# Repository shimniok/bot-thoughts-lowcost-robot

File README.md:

# bot-thoughts-lowcost-robot

Entry for 2012 African Robotics Network Challenge to build a $10, educational robot.

[Bot Thoughts Blog article](https://www.bot-thoughts.com/2012/09/entry-for-afron-10-dollar-robot-design.html)

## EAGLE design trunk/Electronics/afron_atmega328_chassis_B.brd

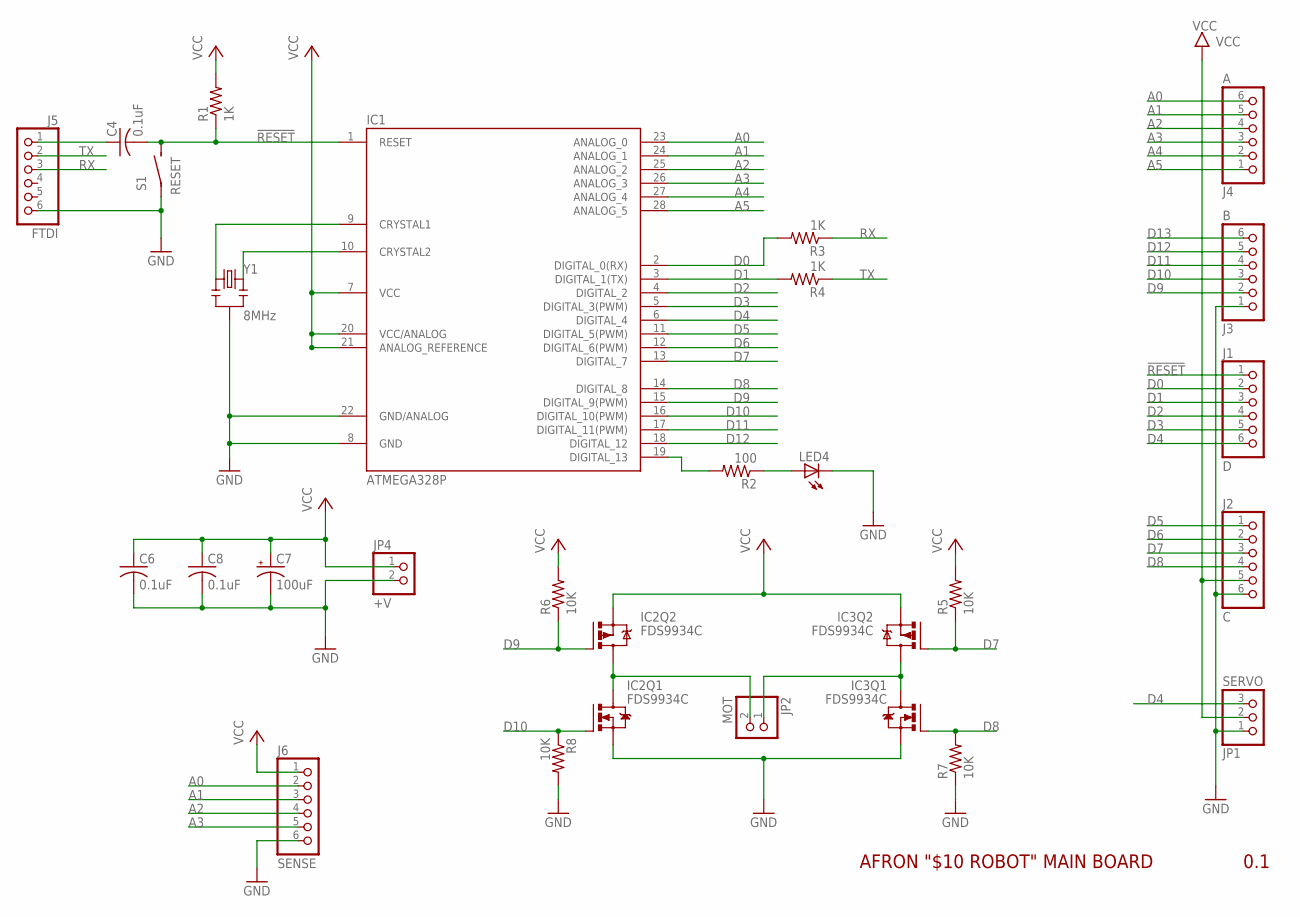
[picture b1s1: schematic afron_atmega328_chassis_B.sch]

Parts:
C4, C6, C8: 0.1uF; C050-024X044
C7: 100uF; E2,5-6
IC1: ATMEGA328P; DIL28-3
IC2, IC3: FDS9934C; SOIC8
J1: D; 1X06
J2: C; 1X06
J3: B; 1X06
J4: A; 1X06
J5: FTDI; 1X06
J6: SENSE; 1X06
JP1: SERVO; 1X03
JP2: MOT; 1X02-S
JP4: +V; 1X02-S
LED4: LED3MM
R1, R3, R4: 1K; 0204/5
R2: 100; 0204/5
R5, R6, R7, R8: 10K; 0204/5
S1: RESET; 6MMTACTILE
Y1: 8MHz; RESONATOR-PTH

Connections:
!RESET: C4.2, IC1.1 (RESET), J1.1, R1.1, S1.P$2 (S)
A0: IC1.23 (ANALOG_0), J4.6, J6.2
A1: IC1.24 (ANALOG_1), J4.5, J6.3
A2: IC1.25 (ANALOG_2), J4.4, J6.4
A3: IC1.26 (ANALOG_3), J4.3, J6.5
A4: IC1.27 (ANALOG_4), J4.2
A5: IC1.28 (ANALOG_5), J4.1
D0: IC1.2 (DIGITAL_0(RX)), J1.2, R3.2
D1: IC1.3 (DIGITAL_1(TX)), J1.3, R4.2
D2: IC1.4 (DIGITAL_2), J1.4
D3: IC1.5 (DIGITAL_3(PWM)), J1.5
D4: IC1.6 (DIGITAL_4), J1.6, JP1.3
D5: IC1.11 (DIGITAL_5(PWM)), J2.1
D6: IC1.12 (DIGITAL_6(PWM)), J2.2
D7: IC1.13 (DIGITAL_7), IC3.4 (G), J2.3, R5.1
D8: IC1.14 (DIGITAL_8), IC3.2 (G), J2.4, R7.2
D9: IC1.15 (DIGITAL_9(PWM)), IC2.4 (G), J3.2, R6.1
D10: IC1.16 (DIGITAL_10(PWM)), IC2.2 (G), J3.3, R8.1
D11: IC1.17 (DIGITAL_11(PWM)), J3.4
D12: IC1.18 (DIGITAL_12), J3.5
D13: IC1.19 (DIGITAL_13), J3.6, R2.2
GND: C6.2, C7.-, C8.2, IC1.8 (GND), IC1.22 (GND/ANALOG), IC2.1 (S), IC3.1 (S), J2.6, J3.1, J5.6, J6.6, JP1.1, JP4.2, LED4.K (C), R7.1, R8.2, S1.P$1, Y1.2
MA: IC2.5 (D), IC2.6 (D), IC2.7 (D), IC2.8 (D), JP2.2
MB: IC3.5 (D), IC3.6 (D), IC3.7 (D), IC3.8 (D), JP2.1
unnamed: IC1.9 (CRYSTAL1), Y1.1
unnamed: IC1.10 (CRYSTAL2), Y1.3
unnamed: C4.1, J5.1
unnamed: LED4.A, R2.1
RX: J5.3, R3.1
TX: J5.2, R4.1
VCC: C6.1, C7.+, C8.1, IC1.7 (VCC), IC1.20 (VCC/ANALOG), IC1.21 (ANALOG_REFERENCE), IC2.3 (S), IC3.3 (S), J2.5, J6.1, JP1.2, JP4.1, R1.2, R5.2, R6.2

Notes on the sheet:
AFRON "$10 ROBOT" MAIN BOARD
0.1

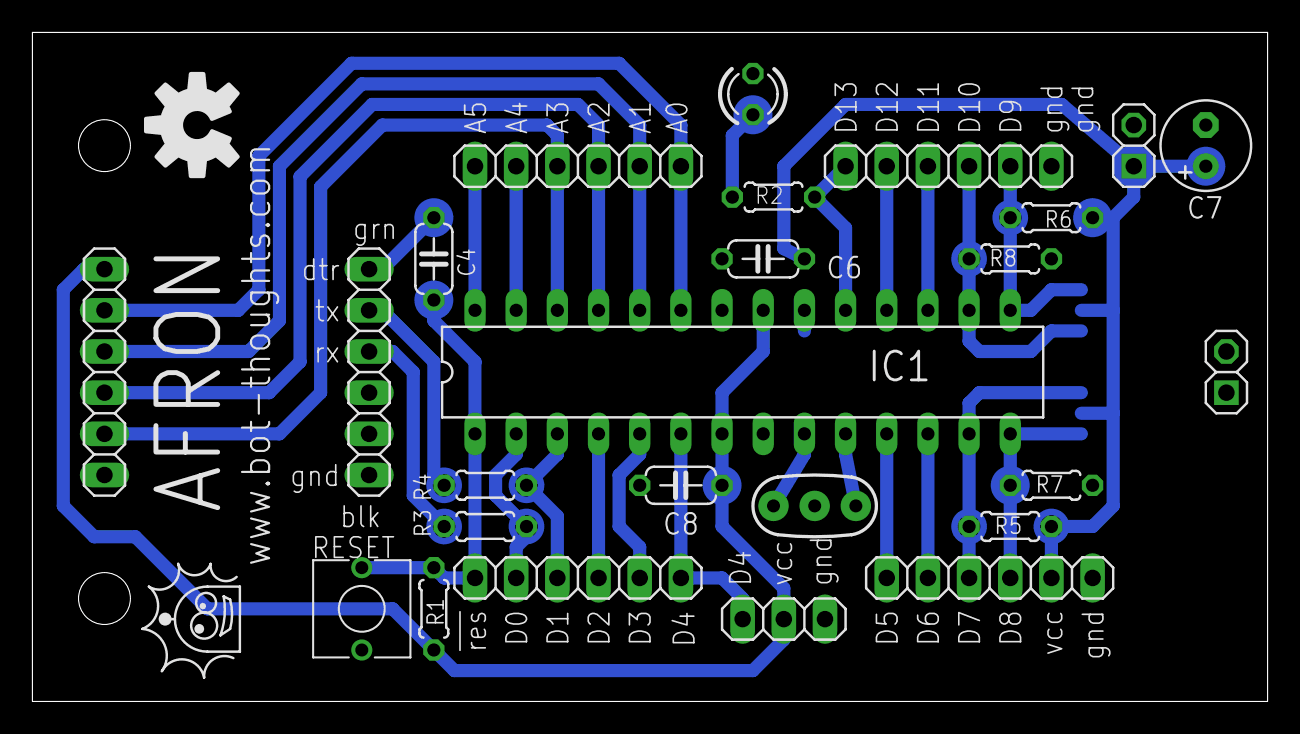
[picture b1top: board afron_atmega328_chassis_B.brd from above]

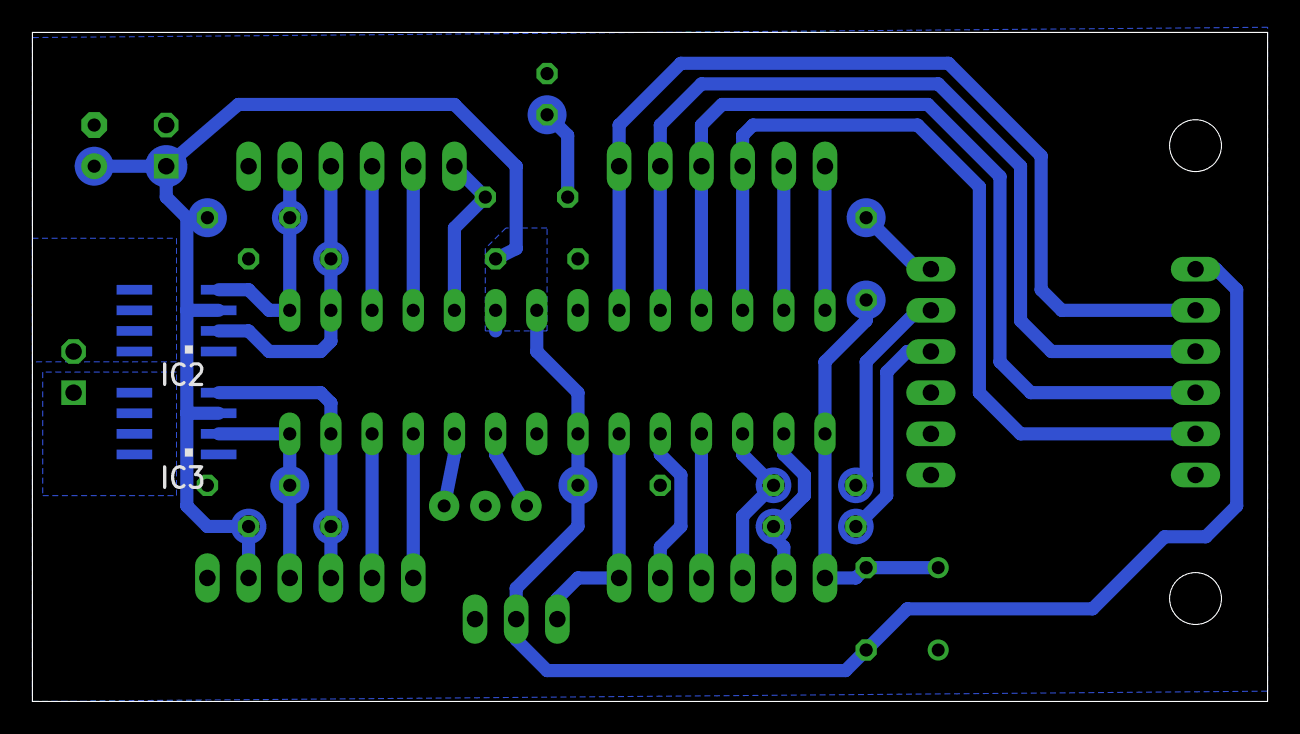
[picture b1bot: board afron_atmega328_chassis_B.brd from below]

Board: 2 copper layers, 76.2 x 41.3 mm, 27 parts (2 on the bottom side), 31 nets.

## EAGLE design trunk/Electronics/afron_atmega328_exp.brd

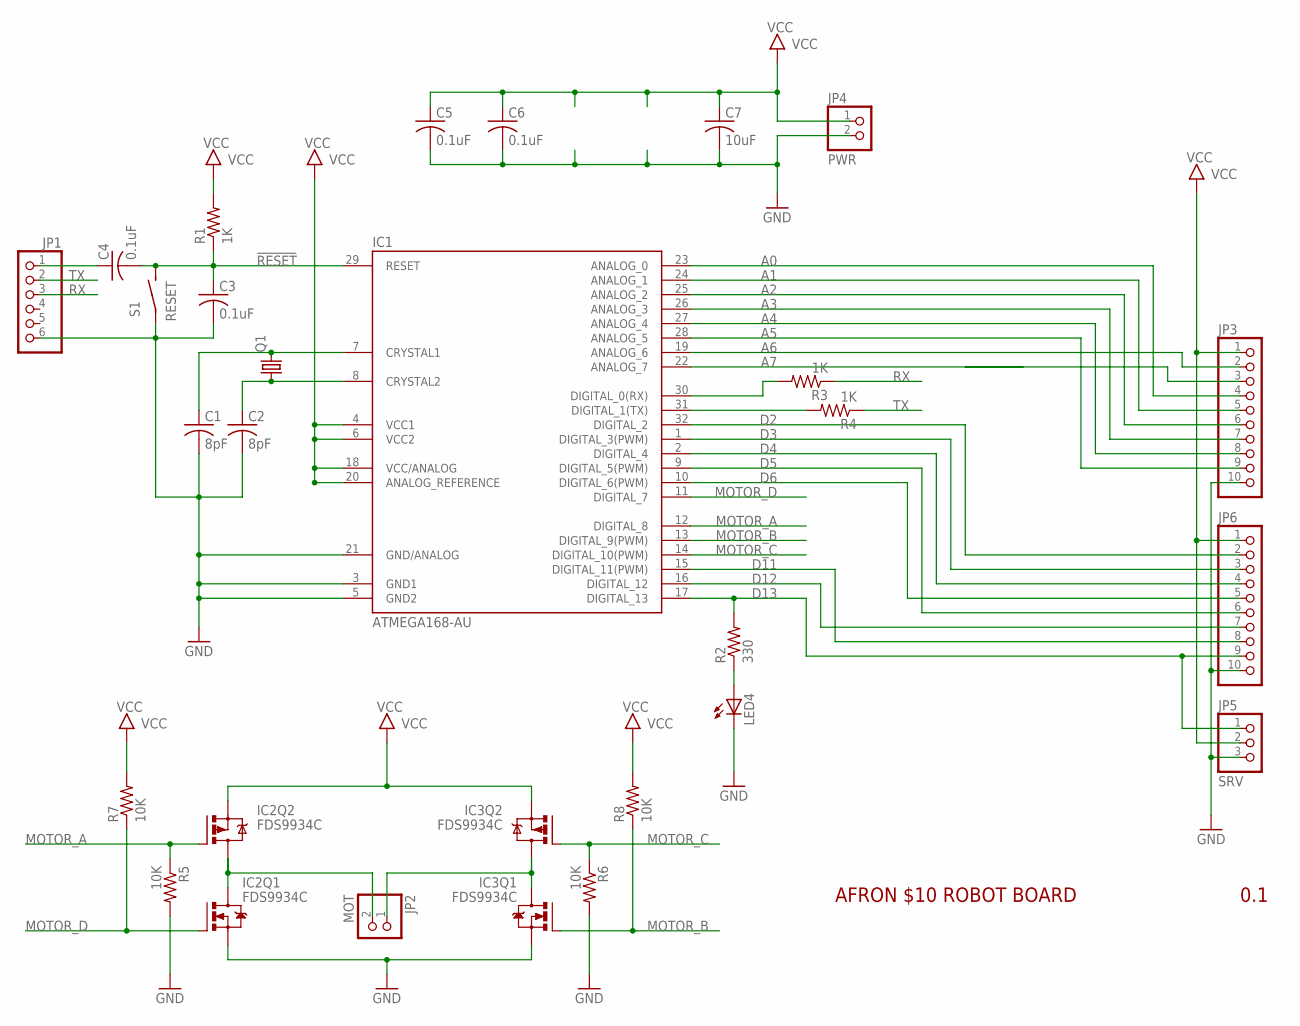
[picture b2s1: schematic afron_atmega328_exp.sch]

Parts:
C1, C2: 8pF; C0603
C3, C4, C5, C6: 0.1uF; C0603
C7: 10uF; C0805
IC1: ATMEGA168-AU; TQFP32-08
IC2, IC3: FDS9934C; SOIC8
JP1: PINHD-1X06_2.54-S; 1X06-S
JP2: MOT; 1X02-S
JP3, JP6: PINHD-1X10_2.54-S; 1X10-S
JP4: PWR; 1X02-S
JP5: SRV; 1X03-S
LED4: LEDSML0805; SML0805
Q1: CRYSTALNDK5X3; NDK_2PAD_5X3
R1, R3, R4: 1K; R0603
R2: 330; R0603
R5, R6, R7, R8: 10K; R0603
S1: RESET; 6MMTACTILE_RECT

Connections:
!RESET: C3.1, C4.2, IC1.29 (RESET), R1.1, S1.P$2 (S)
A0: IC1.23 (ANALOG_0), JP3.4
A1: IC1.24 (ANALOG_1), JP3.5
A2: IC1.25 (ANALOG_2), JP3.6
A3: IC1.26 (ANALOG_3), JP3.7
A4: IC1.27 (ANALOG_4), JP3.8
A5: IC1.28 (ANALOG_5), JP3.9
A6: IC1.19 (ANALOG_6), JP3.2
A7: IC1.22 (ANALOG_7), JP3.3
D2: IC1.32 (DIGITAL_2), JP6.2
D3: IC1.1 (DIGITAL_3(PWM)), JP6.3
D4: IC1.2 (DIGITAL_4), JP6.4
D5: IC1.9 (DIGITAL_5(PWM)), JP6.6
D6: IC1.10 (DIGITAL_6(PWM)), JP6.5
D11: IC1.15 (DIGITAL_11(PWM)), JP6.8
D12: IC1.16 (DIGITAL_12), JP6.7
D13: IC1.17 (DIGITAL_13), JP5.1, JP6.9, R2.2
GND: C1.2, C2.2, C5.2, C6.2, C7.2, IC1.3 (GND1), IC1.5 (GND2), IC1.21 (GND/ANALOG), IC2.1 (S), IC3.1 (S), JP1.6, JP3.10, JP4.2, JP5.3, JP6.10, LED4.C, R5.2, R6.2, S1.P$1
MA: IC2.5 (D), IC2.6 (D), IC2.7 (D), IC2.8 (D), JP2.2
MB: IC3.5 (D), IC3.6 (D), IC3.7 (D), IC3.8 (D), JP2.1
MOTOR_A: IC1.12 (DIGITAL_8), IC2.4 (G), R5.1
MOTOR_B: IC1.13 (DIGITAL_9(PWM)), IC3.2 (G), R8.1
MOTOR_C: IC1.14 (DIGITAL_10(PWM)), IC3.4 (G), R6.1
MOTOR_D: IC1.11 (DIGITAL_7), IC2.2 (G), R7.1
unnamed: C1.1, IC1.7 (CRYSTAL1), Q1.P$2 (2)
unnamed: C2.1, IC1.8 (CRYSTAL2), Q1.P$1 (1)
unnamed: C4.1, JP1.1
unnamed: LED4.A, R2.1
unnamed: IC1.31 (DIGITAL_1(TX)), R4.2
unnamed: IC1.30 (DIGITAL_0(RX)), R3.2
RX: JP1.3, R3.1
TX: JP1.2, R4.1
VCC: C5.1, C6.1, C7.1, IC1.4 (VCC1), IC1.6 (VCC2), IC1.18 (VCC/ANALOG), IC1.20 (ANALOG_REFERENCE), IC2.3 (S), IC3.3 (S), JP3.1, JP4.1, JP5.2, JP6.1, R1.2, R7.2, R8.2

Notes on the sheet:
AFRON $10 ROBOT BOARD
0.1

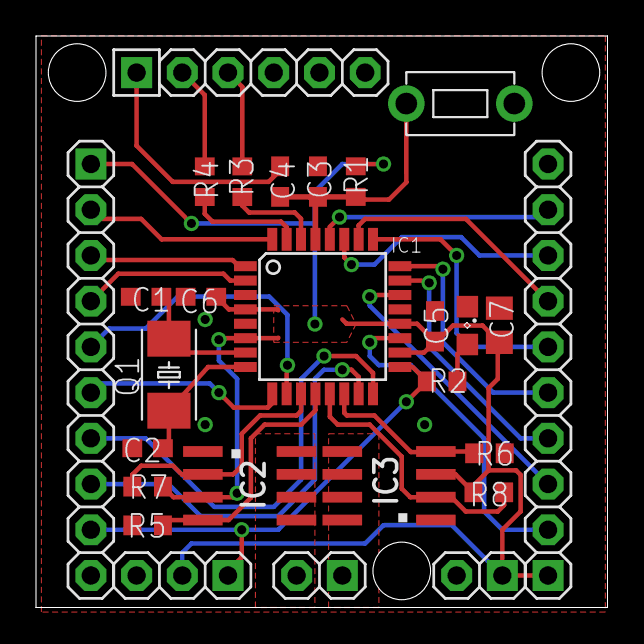
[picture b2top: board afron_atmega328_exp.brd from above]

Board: 2 copper layers, 31.8 x 31.8 mm, 27 parts (0 on the bottom side), 33 nets.

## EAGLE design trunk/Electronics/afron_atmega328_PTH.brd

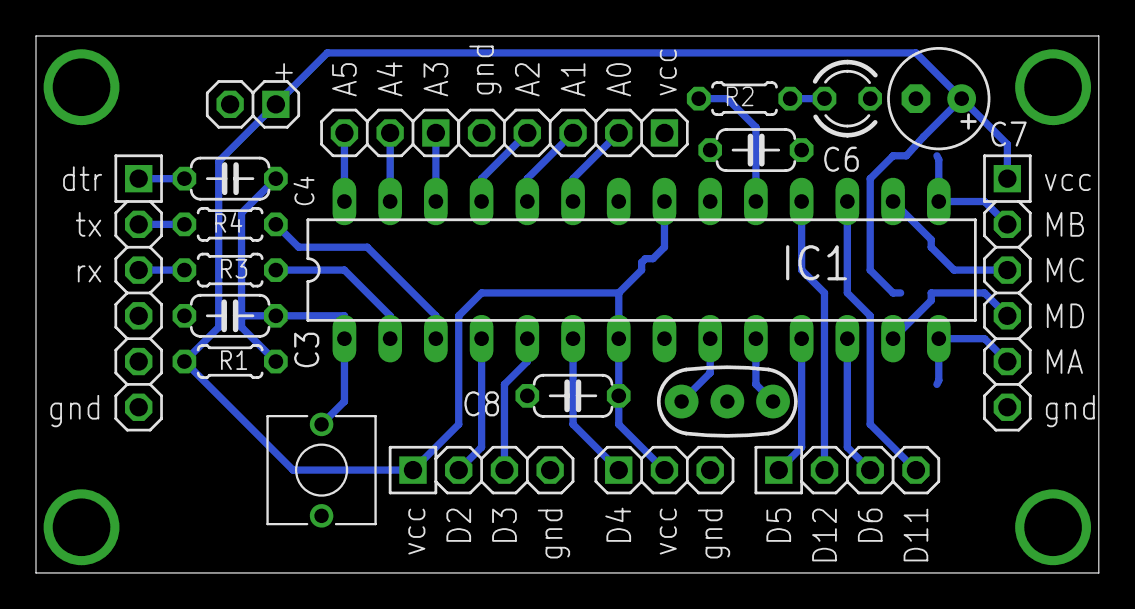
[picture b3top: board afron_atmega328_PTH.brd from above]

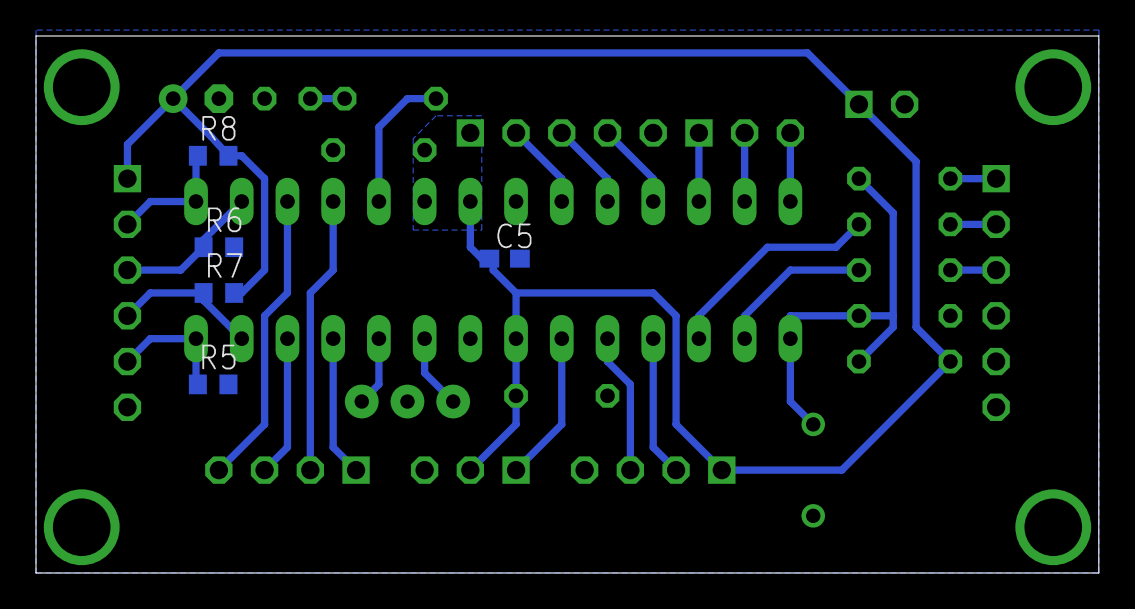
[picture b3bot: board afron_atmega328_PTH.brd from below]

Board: 2 copper layers, 59.0 x 29.8 mm, 26 parts (5 on the bottom side), 29 nets.

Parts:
C3, C4, C6, C8: 0.1uF; C050-024X044
C5: 0.1uF; C0603
C7: 10uF; E2,5-6
IC1: ATMEGA328P; DIL28-3
JP1: 1X06-S
JP2: SWITCH; 1X04-S
JP3: SENSOR; 1X05-S
JP4: PWR; 1X02-S
JP5: SRV; 1X03-S
JP6: MOTOR; 1X06-S
JP7: A; 1X04-S
JP8: B; 1X03-S
LED4: LED3MM
R1, R3, R4: 1K; 0204/5
R2: 330; 0204/5
R5, R6, R7, R8: 10K; R0603
S1: RESET; 6MMTACTILE
Y1: 4MHz; RESONATOR-PTH

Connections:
!RESET: C3.1, C4.2, IC1.1, R1.1, S1.P$2
A0: IC1.23, JP3.2
A1: IC1.24, JP3.3
A2: IC1.25, JP3.4
A3: IC1.26, JP8.1
A4: IC1.27, JP8.2
A5: IC1.28, JP8.3
D2: IC1.4, JP2.2
D3: IC1.5, JP2.3
D4: IC1.6, JP5.1
D5: IC1.11, JP7.1
D6: IC1.12, JP7.3
D11: IC1.17, JP7.4
D12: IC1.18, JP7.2
D13: IC1.19, R2.2
GND: C3.2, C5.2, C6.2, C7.-, C8.2, IC1.8, IC1.22, JP1.6, JP2.4, JP3.5, JP4.2, JP5.3, JP6.6, LED4.K, R5.2, R6.2, S1.P$1, Y1.2
MOTOR_A: IC1.14, JP6.5, R5.1
MOTOR_B: IC1.15, JP6.2, R8.1
MOTOR_C: IC1.16, JP6.3, R6.1
MOTOR_D: IC1.13, JP6.4, R7.1
unnamed: IC1.9, Y1.1
unnamed: IC1.10, Y1.3
unnamed: C4.1, JP1.1
unnamed: LED4.A, R2.1
unnamed: IC1.3, R4.2
unnamed: IC1.2, R3.2
RX: JP1.3, R3.1
TX: JP1.2, R4.1
VCC: C5.1, C6.1, C7.+, C8.1, IC1.7, IC1.20, IC1.21, JP2.1, JP3.1, JP4.1, JP5.2, JP6.1, R1.2, R7.2, R8.2

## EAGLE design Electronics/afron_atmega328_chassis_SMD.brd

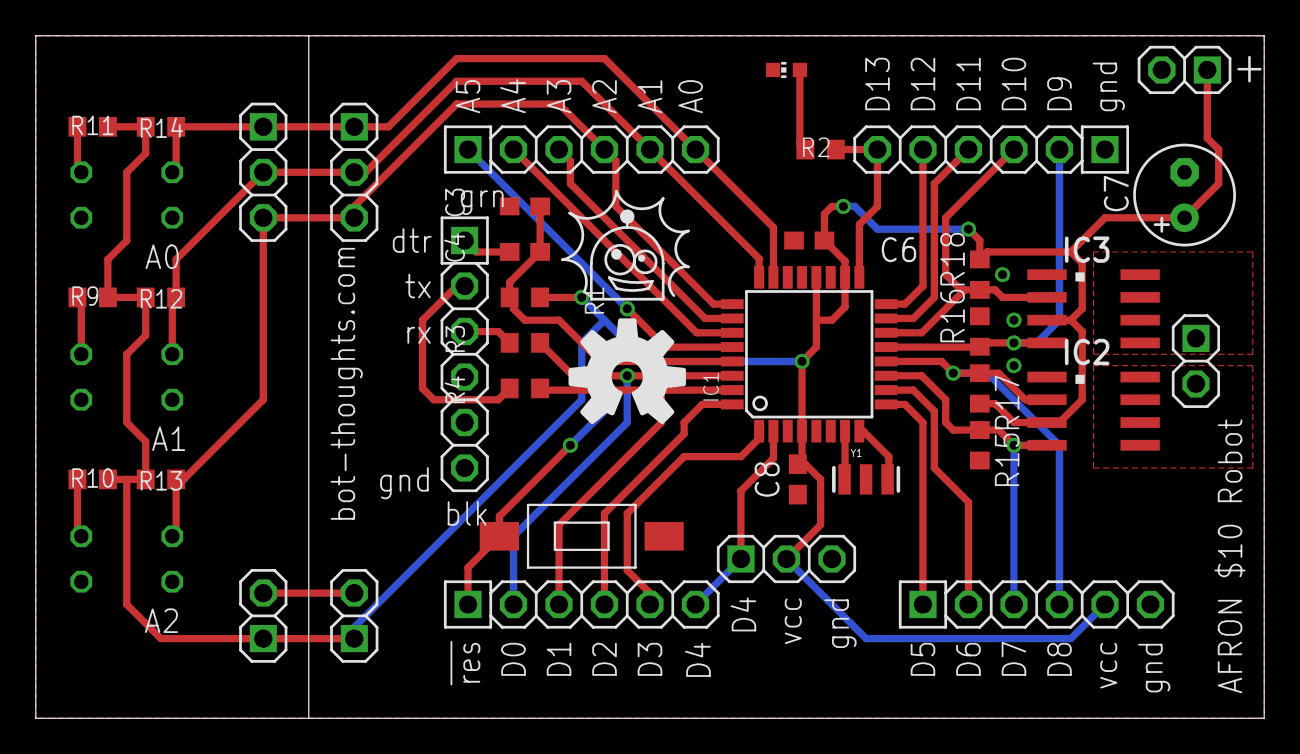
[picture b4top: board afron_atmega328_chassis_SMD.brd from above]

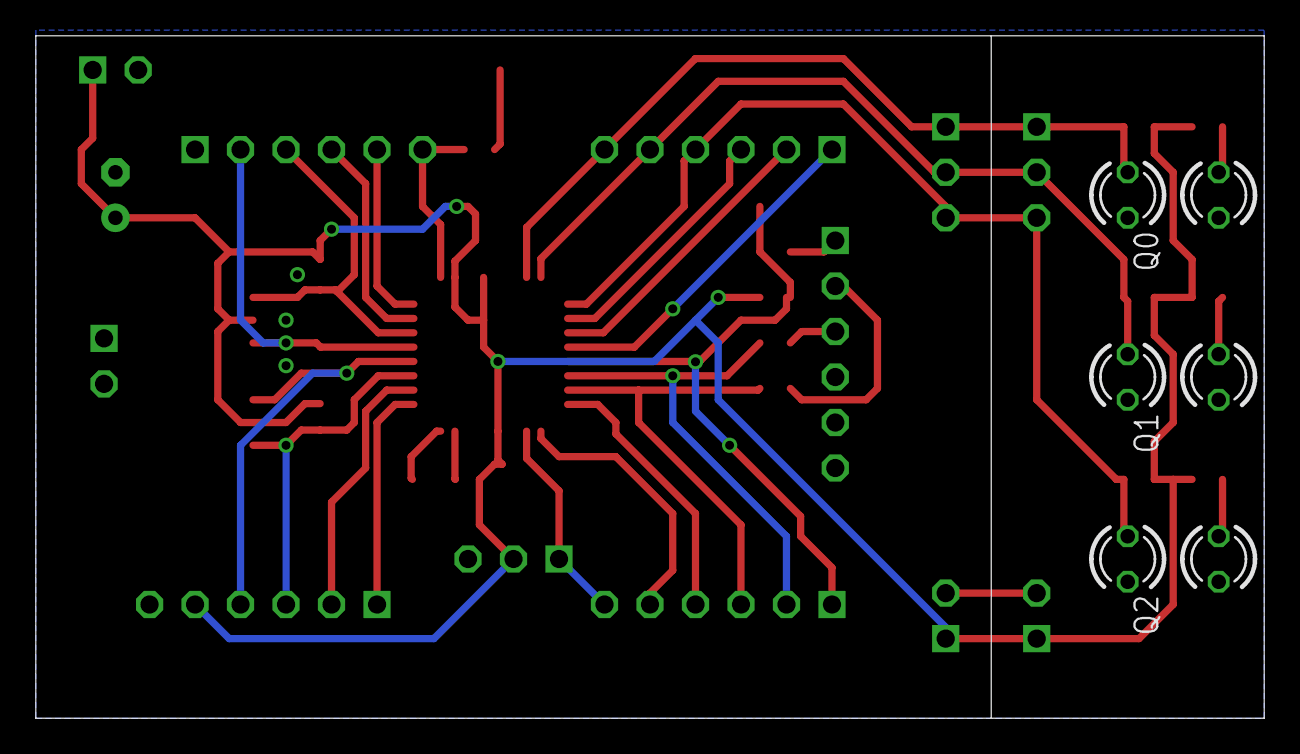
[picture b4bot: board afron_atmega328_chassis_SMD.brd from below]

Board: 2 copper layers, 68.6 x 38.1 mm, 43 parts (6 on the bottom side), 34 nets.

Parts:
C3, C4, C6, C8: 0.1uF; C0603
C7: 10uF; E2,5-6
IC1: ATMEGA168-AU; TQFP32-08
IC2, IC3: FDS9934C; SOIC8
J1: D; 1X06-S
J2: C; 1X06-S
J3: B; 1X06-S
J4: A; 1X06-S
J5: FTDI; 1X06-S
JP1, JP4, JP6: PWR; 1X02-S
JP2: MOT; 1X02-S
JP3, JP7: SENS; 1X03-S
JP5: SRV; 1X03-S
LED0, LED1, LED2: LED3MM
LED4: CHIP-LED0603
Q0, Q1, Q2: LED3MM
R1, R3, R4: 1K; R0603
R2, R9, R10, R11: 100; R0603
R12, R13, R14, R15, R16, R17, R18: 10K; R0603
S1: RESET; 6MMTACTTILE_RECT_SMD
Y1: 4MHz; RESONATOR-SMD

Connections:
!RESET: C3.1, C4.2, IC1.29, J1.1, R1.1, S1.P$2
A0: IC1.23, J4.6, JP3.1, JP7.1, Q0.A, R14.1
A1: IC1.24, J4.5, JP3.2, JP7.2, Q1.A, R12.1
A2: IC1.25, J4.4, JP3.3, JP7.3, Q2.A, R13.1
A3: IC1.26, J4.3
A4: IC1.27, J4.2
A5: IC1.28, J4.1
D0: IC1.30, J1.2, R3.2
D1: IC1.31, J1.3, R4.2
D2: IC1.32, J1.4
D3: IC1.1, J1.5
D4: IC1.2, J1.6, JP5.1
D5: IC1.9, J2.1
D6: IC1.10, J2.2
D7: IC1.11, IC2.4, J2.3, R15.1
D8: IC1.12, IC2.2, J2.4, R17.1
D9: IC1.13, IC3.4, J3.2, R16.1
D10: IC1.14, IC3.2, J3.3, R18.1
D11: IC1.15, J3.4
D12: IC1.16, J3.5
D13: IC1.17, J3.6, R2.2
GND: C3.2, C6.2, C8.2, IC1.3, IC1.21, IC2.1, IC3.1, J2.6, J3.1, J5.6, JP1.2, JP4.2, JP5.3, JP6.2, LED0.K, LED1.K, LED2.K, LED4.C, Q0.K, Q1.K, Q2.K, R15.2, R16.2, S1.P$1, Y1.2
MA: IC2.5, IC2.6, IC2.7, IC2.8, JP2.2
MB: IC3.5, IC3.6, IC3.7, IC3.8, JP2.1
unnamed: LED0.A, R11.1
unnamed: IC1.7, Y1.1
unnamed: IC1.8, Y1.3
unnamed: C4.1, J5.1
unnamed: LED2.A, R10.1
unnamed: LED4.A, R2.1
unnamed: LED1.A, R9.1
RX: J5.3, R3.1
TX: J5.2, R4.1
VCC: C6.1, C8.1, IC1.4, IC1.18, IC1.20, IC2.3, IC3.3, J2.5, JP1.1, JP4.1, JP5.2, JP6.1, R1.2, R9.2, R10.2, R11.2, R12.2, R13.2, R14.2, R17.2, R18.2

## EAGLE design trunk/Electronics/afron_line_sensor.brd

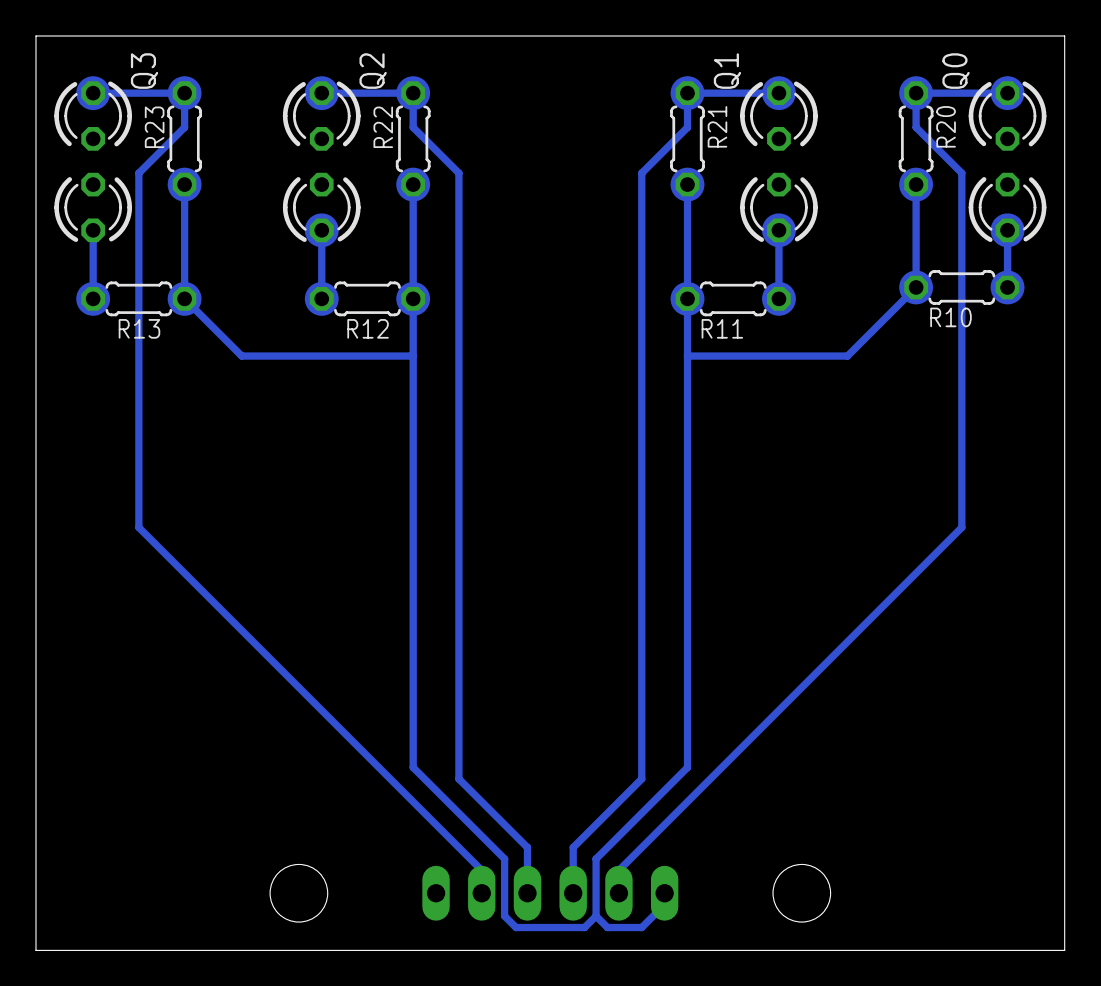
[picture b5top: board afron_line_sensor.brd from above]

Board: 2 copper layers, 57.1 x 50.8 mm, 17 parts (1 on the bottom side), 10 nets.

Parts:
JP1: 1X06
LED0, LED1, LED2, LED3: LED3MM
Q0, Q1, Q2, Q3: LED3MM
R10, R11, R12, R13: 100; 0204/5
R20, R21, R22, R23: 10K; 0204/5

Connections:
GND: JP1.6, LED0.K, LED1.K, LED2.K, LED3.K, Q0.K, Q1.K, Q2.K, Q3.K
unnamed: LED0.A, R10.1
unnamed: LED2.A, R12.1
unnamed: LED3.A, R13.1
unnamed: LED1.A, R11.1
SENSE0: JP1.2, Q0.A, R20.1
SENSE1: JP1.3, Q1.A, R21.1
SENSE2: JP1.4, Q2.A, R22.1
SENSE3: JP1.5, Q3.A, R23.1
VCC: JP1.1, R10.2, R11.2, R12.2, R13.2, R20.2, R21.2, R22.2, R23.2

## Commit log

2012-09-14 Initial directory structure.
2012-09-14 Initial revision
2012-09-14 didn't need this file
2012-09-14 Revised with some comments
2015-05-04 Migrating wiki contents from Google Code
2021-02-11 added missing software and documents

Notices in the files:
parts and their libraries:
SparkFun: Licensing: CC v3.0 Share-Alike You are welcome to use this library for commercial purposes.
